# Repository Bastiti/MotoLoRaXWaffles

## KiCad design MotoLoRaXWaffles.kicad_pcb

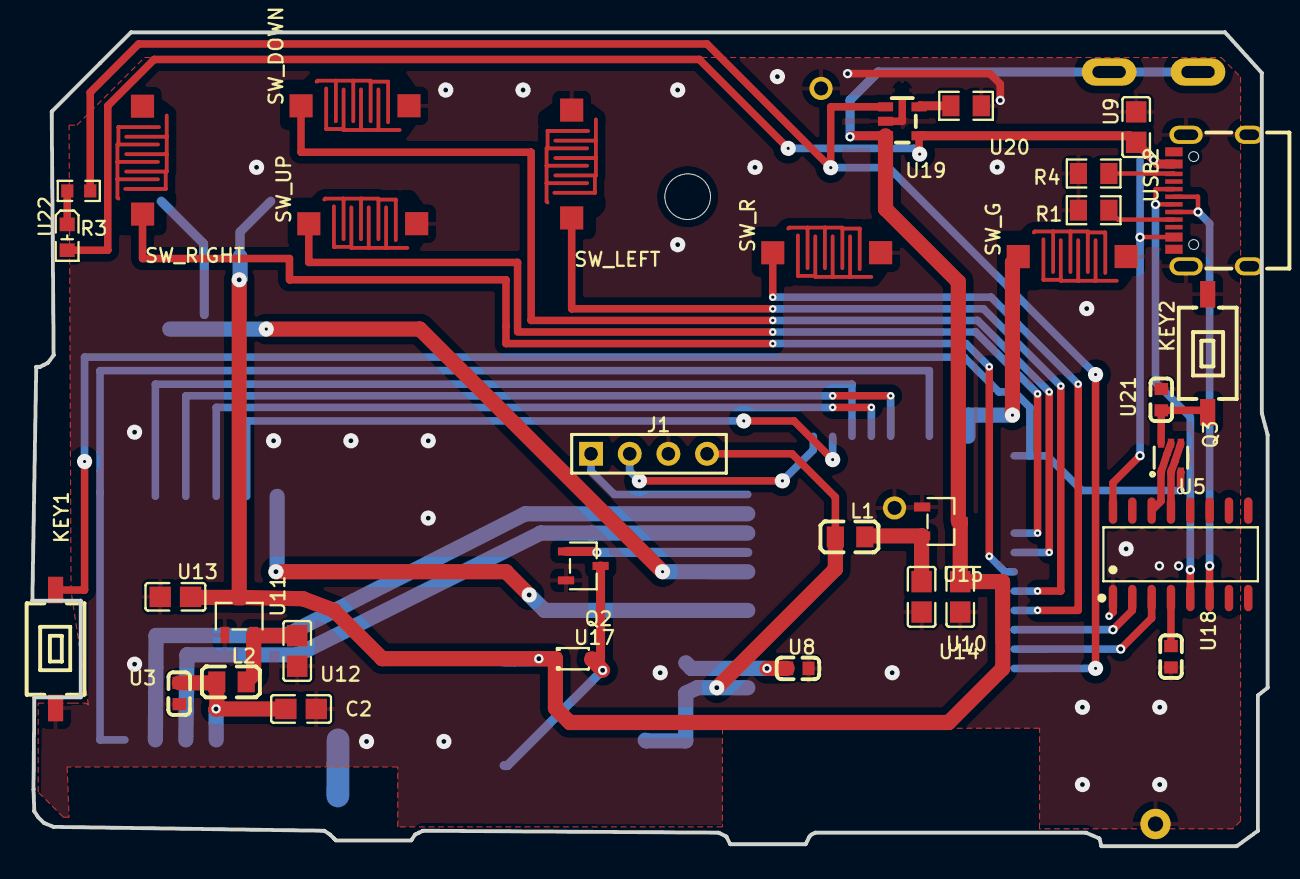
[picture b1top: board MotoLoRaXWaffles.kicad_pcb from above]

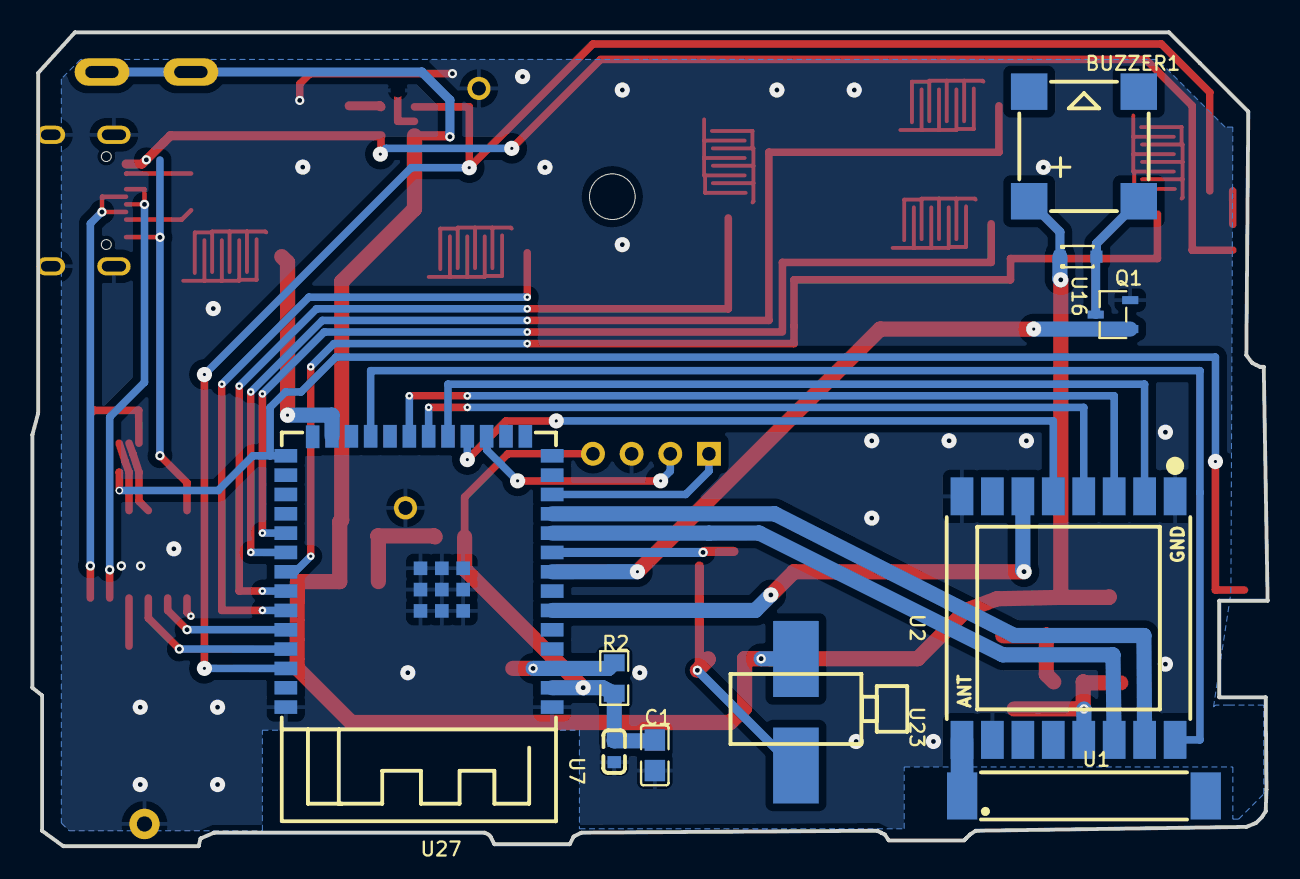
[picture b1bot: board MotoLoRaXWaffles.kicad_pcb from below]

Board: 2 copper layers, 81.2 x 53.5 mm, 49 parts (10 on the bottom side), 43 nets.

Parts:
BT1: r; AAA_MOTOROLA_ADVISDOR_LINGUIST
BUZZER1: 2700Hz; BUZ-SMD_4P-L8.5-W8.5-P8.50-BR
C1, C2: 10uF; C0805
J1: HDR-M-2.54_1x4; HDR-M-2.54_1X4
KEY1, KEY2: BUTTON2-3*6*2.5; SW-SMD_L6.0-W3.7-LS8.0
L1, L2: 600Ω; L0805
Pad_gge6166: Pad_gge6166
Pad_gge29981: Pad_gge29981
Pad_gge30020: Pad_gge30020
Pad_gge30041: Pad_gge30041
Q1, Q2: AO3400A; SOT-23-3_L3.0-W1.6-P1.90-LS2.8-BR
Q3: UMH3N; SC-70-6_L2.2-W1.3-P0.65-LS2.1-BR
R1, R4: 5.1kΩ; R0805
R2: 10kΩ; R0805
R3: 270ohms; R0603
SW_DOWN: BUTTON; PUSH_BUTTON_MOTOLORA
SW_G: BUTTON; PUSH_BUTTON_MOTOLORA
SW_LEFT: BUTTON; PUSH_BUTTON_MOTOLORA
SW_R: BUTTON; PUSH_BUTTON_MOTOLORA
SW_RIGHT: BUTTON; PUSH_BUTTON_MOTOLORA
SW_UP: BUTTON; PUSH_BUTTON_MOTOLORA
U1: AN1603-433; ANT-SMD_L16.0-W3.1
U2: SX1278S43S+T-X1; WIRELM-SMD_SX1278S165SY-T-X1
U3, U7, U18: 100nF; C0603
U5: CH340C; SOP-16_L10.0-W3.9-P1.27-LS6.0-BL
U8: 1uF; C0603
U9, U10, U12, U13, U14: 1uF; C0805
U11, U15: MD57E33QA3; SOT-23-3_L2.9-W1.6-P1.90-LS2.8-BR
U16, U17: 1N4148WF; SOD-323FL_L1.7-W1.3-LS2.5-RD
U19: TP4054S5; SOT-23-5_L2.9-W1.6-P0.95-LS2.8-BR
U20: 2.2kΩ; R0805
U21: 10uF; C0603
U22: APT1608SRCPRV; LED0603-FD
U23: LCM04084521-B1; MOTOR_LCM04084521-B1
U27: ESP32-S3-WROOM-1(N8R2); WIRELM-SMD_ESP32-S3-WROOM-1
USB2: CQ-USB- TYPE-C 16P母座四脚插板有柱; USB-C-SMD_CQ-USB-TYPE-C

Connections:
3.3V: C1.2, J1.4, L1.1, R2.1, U7.2, U27.2
3.3V_RF: C2.2, L2.1, U2.13, U3.2
+5V: U5.16, U9.1, U19.4, U22.1, USB2.A4B9, USB2.B4A9
BATT: BT1.P, BUZZER1.1, U10.2, U11.3, U13.2, U15.3, U16.1, U17.1, U19.3, U23.1
BTN-DOWN: SW_DOWN.1, U27.32
BTN-GREEN: SW_G.1, U27.25
BTN-LEFT: SW_LEFT.1, U27.34
BTN-RED: SW_R.1, U27.35
BTN-RIGHT: SW_RIGHT.1, U27.33
BTN-UP: SW_UP.1, U27.31
BUZZER: Q1.1, U27.8
BUZZER1_2: BUZZER1.2, Q1.3, U16.2
CHARG: R3.1, U19.1, U27.38
D+: U5.5, USB2.A6, USB2.B6
D-: U5.6, USB2.A7, USB2.B7
DTR: Q3.2, Q3.4, U5.13
ESP32_CK: U2.4, U27.20
ESP32_MISO: U2.3, U27.21
ESP32_MOSI: U2.2, U27.19
ESP32_RX: U5.2, U27.36
ESP32_SCL: J1.2, U27.17
ESP32_SDA: J1.1, U27.12
ESP32_TX: U5.3, U27.37
GND: BT1.N, C1.1, C2.1, J1.3, KEY1.2, KEY2.2, Pad_gge29981.3, Pad_gge30020.3, Pad_gge30041.3, Q1.2, Q2.2, R1.1, R4.1, SW_DOWN.2, SW_G.2, SW_LEFT.2, SW_R.2, SW_RIGHT.2, SW_UP.2, U2.1, U2.8, U2.10, U3.1, U5.1, U7.1, U8.1, U9.2, U10.1, U11.1, U12.1, U13.1, U14.1, U15.1, U18.2, U19.2, U20.1, U21.2, U27.1, U27.40, U27.41, USB2.0, USB2.A1B12, USB2.B1A12
IO0: KEY1.1, Q3.3, U27.27
MOTOR: Q2.1, U27.9
R3_2: R3.2, U22.2
RADIO_CS: U2.5, U27.18
RADIO_DIO0: U2.14, U27.10
RADIO_DIO1: U2.15, U27.11
RADIO_DIO2: U2.16, U27.23
RADIO_RST: U2.6, U27.6
RST: KEY2.1, Q3.6, U21.1
RTS: Q3.1, Q3.5, U5.14
U1_1: U1.1, U2.9
U5_4: U5.4, U18.1
U8_2: R2.2, U8.2, U27.3
U11_2: L2.2, U11.2, U12.2
U14_2: L1.2, U14.2, U15.2
U17_2: Q2.3, U17.2, U23.2
U19_5: U19.5, U20.2
USB2_A5: R1.2, USB2.A5
USB2_B5: R4.2, USB2.B5

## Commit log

2025-01-31 Added PDF Files
